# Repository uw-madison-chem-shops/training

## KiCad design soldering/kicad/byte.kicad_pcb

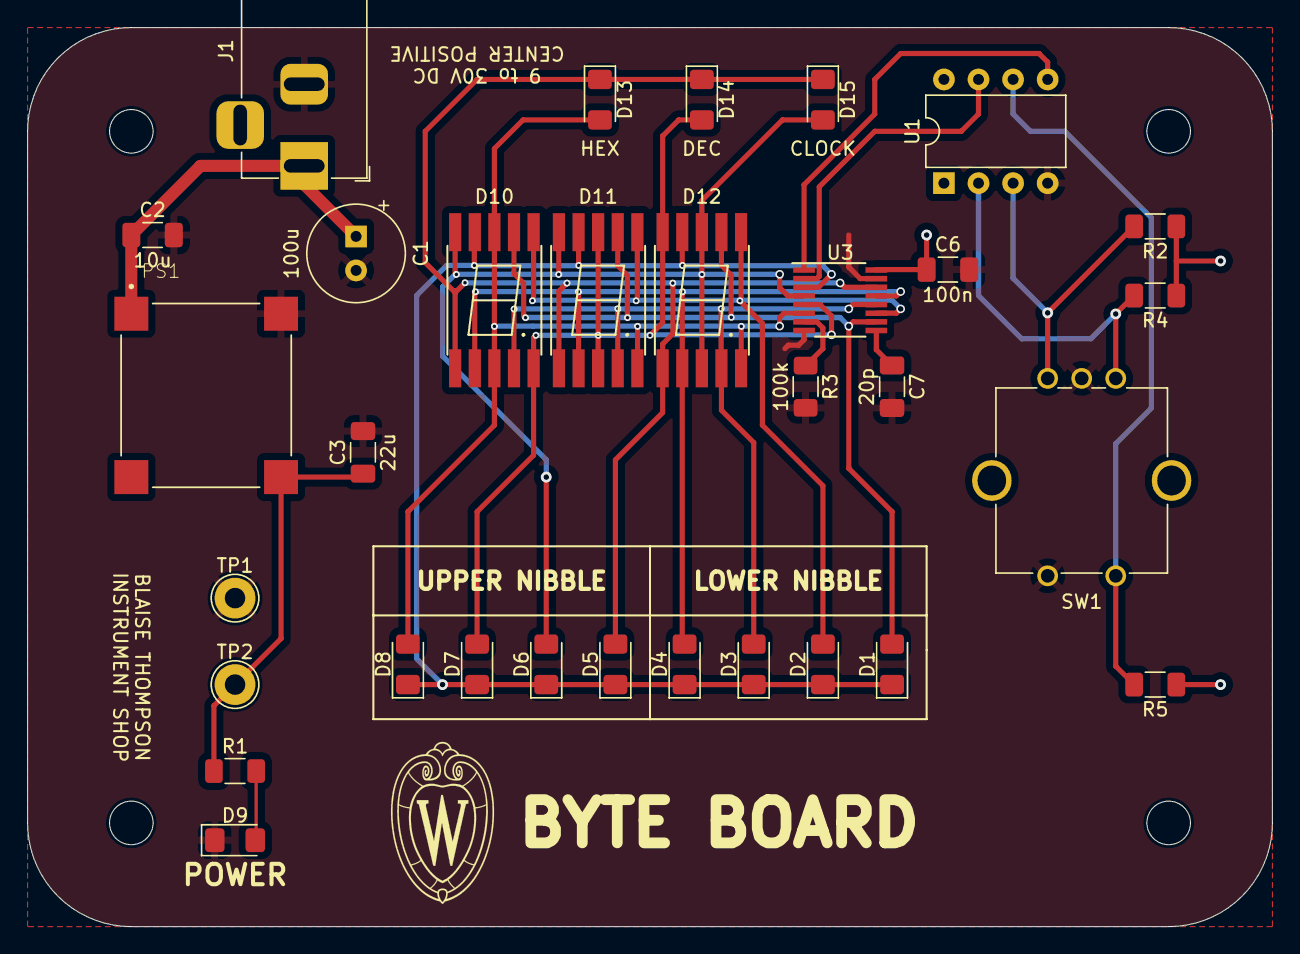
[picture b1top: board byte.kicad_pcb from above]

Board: 2 copper layers, 91.4 x 66.0 mm, 32 parts (0 on the bottom side), 20 nets.

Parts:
C1: 100u; CP_Radial_Tantal_D7.0mm_P2.50mm
C2: 10u; C_1206_3216Metric_Pad1.33x1.80mm_HandSolder
C3: 22u; C_1206_3216Metric_Pad1.33x1.80mm_HandSolder
C6: 100n; C_1206_3216Metric_Pad1.33x1.80mm_HandSolder
C7: 20p; C_1206_3216Metric_Pad1.33x1.80mm_HandSolder
D1, D2, D3, D4, D5, D6, D7, D8, D9: LED; LED_1206_3216Metric_Pad1.42x1.75mm_HandSolder
D10, D11, D12: ACSC02-41SURKWA-F01
D13: HEX; LED_1206_3216Metric_Pad1.42x1.75mm_HandSolder
D14: DEC; LED_1206_3216Metric_Pad1.42x1.75mm_HandSolder
D15: CLOCK; LED_1206_3216Metric_Pad1.42x1.75mm_HandSolder
J1: Barrel_Jack; BarrelJack_Horizontal
PS1: VXO7803-500-M; CONV_VXO7805-500-M
R1: 1k; R_1206_3216Metric_Pad1.30x1.75mm_HandSolder
R2, R4, R5: 4k7; R_1206_3216Metric_Pad1.30x1.75mm_HandSolder
R3: 100k; R_1206_3216Metric_Pad1.30x1.75mm_HandSolder
SW1: RotaryEncoder_Switch; RotaryEncoder_Bourns_Vertical_PEC12R-3xxxF-Sxxxx
TP1, TP2: TestPoint; TestPoint_THTPad_D3.0mm_Drill1.5mm
U1: ATtiny85-20P; DIP-8_W7.62mm
U3: MAX6951; QSOP-16_3.9x4.9mm_P0.635mm

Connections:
+3V3: C3.1, C6.1, PS1.3 (+VO), R1.1, R2.1, R4.1, R5.1, TP2.1, U1.8 (VCC), U3.16 (V+)
/LED_driver/SEG0: D8.2 (A), D10.3 (C.K.), D10.8 (C.K.), D11.5 (DP), D12.5 (DP), D13.2 (A), U3.6 (DIG0/SEG0)
/LED_driver/SEG1: D7.2 (A), D10.5 (DP), D11.3 (C.K.), D11.8 (C.K.), D12.10 (g), D14.2 (A), U3.5 (DIG1/SEG1)
/LED_driver/SEG2: D6.2 (A), D10.10 (g), D11.10 (g), D12.3 (C.K.), D12.8 (C.K.), D15.2 (A), U3.4 (DIG2/SEG2)
/LED_driver/SEG3: D1.1 (K), D2.1 (K), D3.1 (K), D4.1 (K), D5.1 (K), D6.1 (K), D7.1 (K), D8.1 (K), D10.9 (f), D11.9 (f), D12.9 (f), U3.3 (DIG3/SEG3)
/LED_driver/SEG4: D5.2 (A), D10.1 (e), D11.1 (e), D12.1 (e), D13.1 (K), D14.1 (K), D15.1 (K), U3.14 (DIG4/SEG4)
/LED_driver/SEG5: D4.2 (A), D10.2 (d), D11.2 (d), D12.2 (d), U3.13 (DIG5/SEG5)
/LED_driver/SEG6: D3.2 (A), D10.4 (c), D11.4 (c), D12.4 (c), U3.12 (DIG6/SEG6)
/LED_driver/SEG7: D2.2 (A), D10.6 (b), D11.6 (b), D12.6 (b), U3.11 (DIG7/SEG7)
/LED_driver/SEG8: D1.2 (A), D10.7 (a), D11.7 (a), D12.7 (a), U3.10 (SEG8)
A: R4.2, SW1.A, U1.2 (XTAL1/PB3)
B: R2.2, SW1.B, U1.3 (XTAL2/PB4)
CLK: U1.7 (PB2), U3.2 (CLK)
GND: C1.2, C2.2, C3.2, C6.2, C7.2, D9.1 (K), J1.2, PS1.2 (GND), R3.2, SW1.C, SW1.S2, TP1.1, U1.4 (GND), U3.8 (GND), U3.15 (~CS)
MOSI: U1.5 (AREF/PB0), U3.1 (DIN)
unnamed: D9.2 (A), R1.2
unnamed: C1.1, C2.1, J1.1, PS1.1 (+VIN)
unnamed: R3.1, U3.7 (ISET)
unnamed: C7.1, U3.9 (OSC)
SWITCH: R5.2, SW1.S1, U1.6 (PB1)

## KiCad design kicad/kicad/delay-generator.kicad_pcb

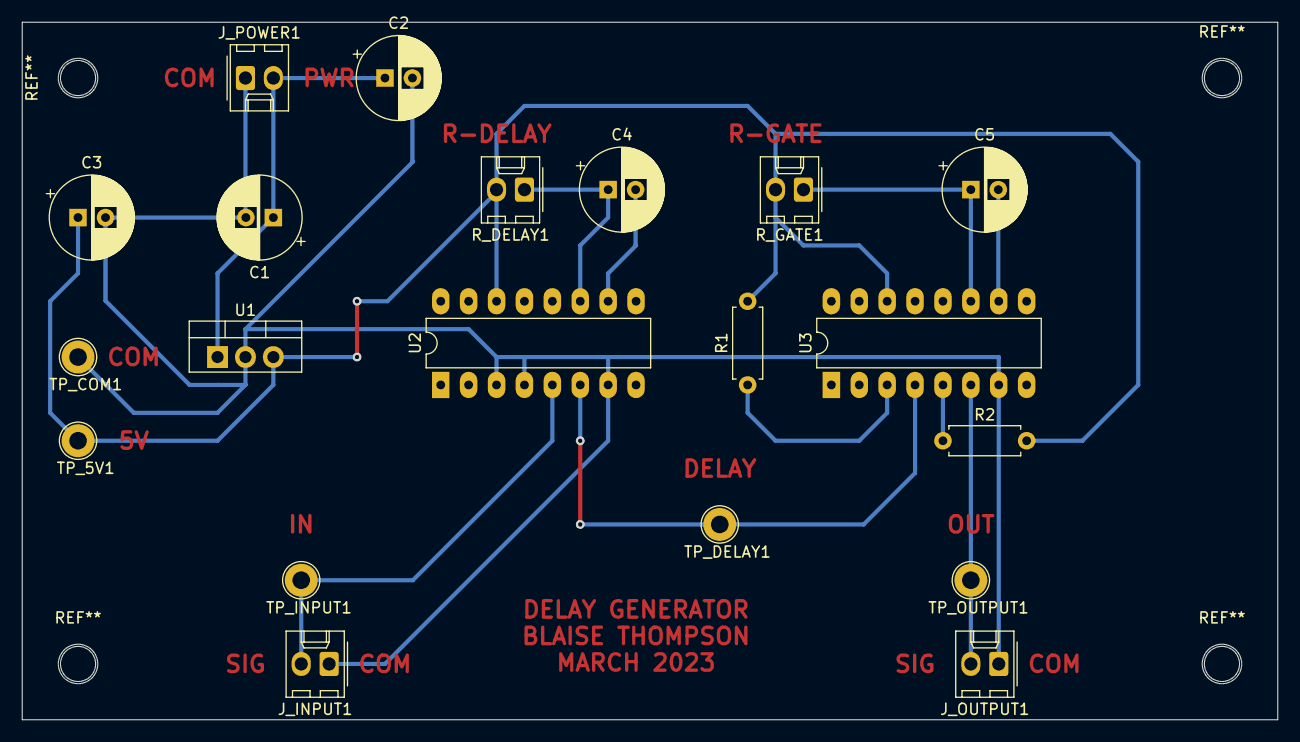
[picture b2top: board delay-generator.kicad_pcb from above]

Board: 2 copper layers, 114.3 x 63.5 mm, 20 parts (0 on the bottom side), 12 nets.

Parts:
C1: 100uF; CP_Radial_D7.5mm_P2.50mm
C2: 330nF; CP_Radial_D7.5mm_P2.50mm
C3, C5: 100nF; CP_Radial_D7.5mm_P2.50mm
C4: 1uF; CP_Radial_D7.5mm_P2.50mm
J_INPUT1: Conn_01x02; Molex_KK-254_AE-6410-02A_1x02_P2.54mm_Vertical
J_OUTPUT1: Conn_01x0; Molex_KK-254_AE-6410-02A_1x02_P2.54mm_Vertical
J_POWER1: Conn_01x02; Molex_KK-254_AE-6410-02A_1x02_P2.54mm_Vertical
R1, R2: 1k; R_Axial_DIN0207_L6.3mm_D2.5mm_P7.62mm_Horizontal
R_DELAY1: 10k; Molex_KK-254_AE-6410-02A_1x02_P2.54mm_Vertical
R_GATE1: 10; Molex_KK-254_AE-6410-02A_1x02_P2.54mm_Vertical
TP_5V1: TestPoint; TestPoint_Loop_D2.60mm_Drill1.6mm_Beaded
TP_COM1: TestPoint; TestPoint_Loop_D2.60mm_Drill1.6mm_Beaded
TP_DELAY1: TestPoint; TestPoint_Loop_D2.60mm_Drill1.6mm_Beaded
TP_INPUT1: TestPoint; TestPoint_Loop_D2.60mm_Drill1.6mm_Beaded
TP_OUTPUT1: TestPoint; TestPoint_Loop_D2.60mm_Drill1.6mm_Beaded
U1: L7805; TO-220-3_Vertical
U2, U3: 74LS121; DIP-16_W7.62mm_LongPads

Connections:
+5V: C3.1, R1.2, R2.2, R_DELAY1.2, R_GATE1.2, TP_5V1.1, U1.3, U2.14, U3.14
GND: C1.2, C2.2, C3.2, J_INPUT1.1, J_OUTPUT1.1, J_POWER1.1, TP_COM1.1, U1.2, U2.3, U2.4, U2.7, U3.7
unnamed: C1.1, C2.1, J_POWER1.2, U1.1
unnamed: C4.1, R_DELAY1.1, U2.11
unnamed: C4.2, U2.10
unnamed: C5.1, R_GATE1.1, U3.11
unnamed: C5.2, U3.10
unnamed: J_INPUT1.2, TP_INPUT1.1, U2.5
unnamed: J_OUTPUT1.2, TP_OUTPUT1.1, U3.6
unnamed: R1.1, U3.3
unnamed: R2.1, U3.5
unnamed: TP_DELAY1.1, U2.6, U3.4

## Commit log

2021-12-06 copy paste
2021-12-06 3d printing
2021-12-15 3d printing update
2021-12-15 add Amber to repair policy
2022-01-25 tool drawers
2022-02-28 flyers
2022-03-01 part numbers
2022-03-11 uprintse
2022-03-17 more examples
2022-03-21 kicad
2022-03-21 3d printing draft
2022-04-07 plumbing
2022-04-07 comma
2022-06-17 yaq training presentation
2022-06-17 fix yaq presentation errors
2022-06-20 fasteners flyer
2022-06-22 yaq training teacher notes
2023-02-17 mqtt
2023-03-27 pcb training
2023-06-06 soldering
2023-07-05 3D printing august
2023-07-21 frameworks september
2023-08-16 soldering presentation
2023-08-16 presentation
2023-10-25 prep for 3D print training
2024-10-18 checkpoint
